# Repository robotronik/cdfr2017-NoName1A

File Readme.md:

$git clone https://github.com/robotronik/cdfr2017-NoName1A

$git add [les fichiers]
ou : $git add -u : tous les fichers modifiés

$git commit -m"le message de commit"

$git push origin master

$git pull origin master

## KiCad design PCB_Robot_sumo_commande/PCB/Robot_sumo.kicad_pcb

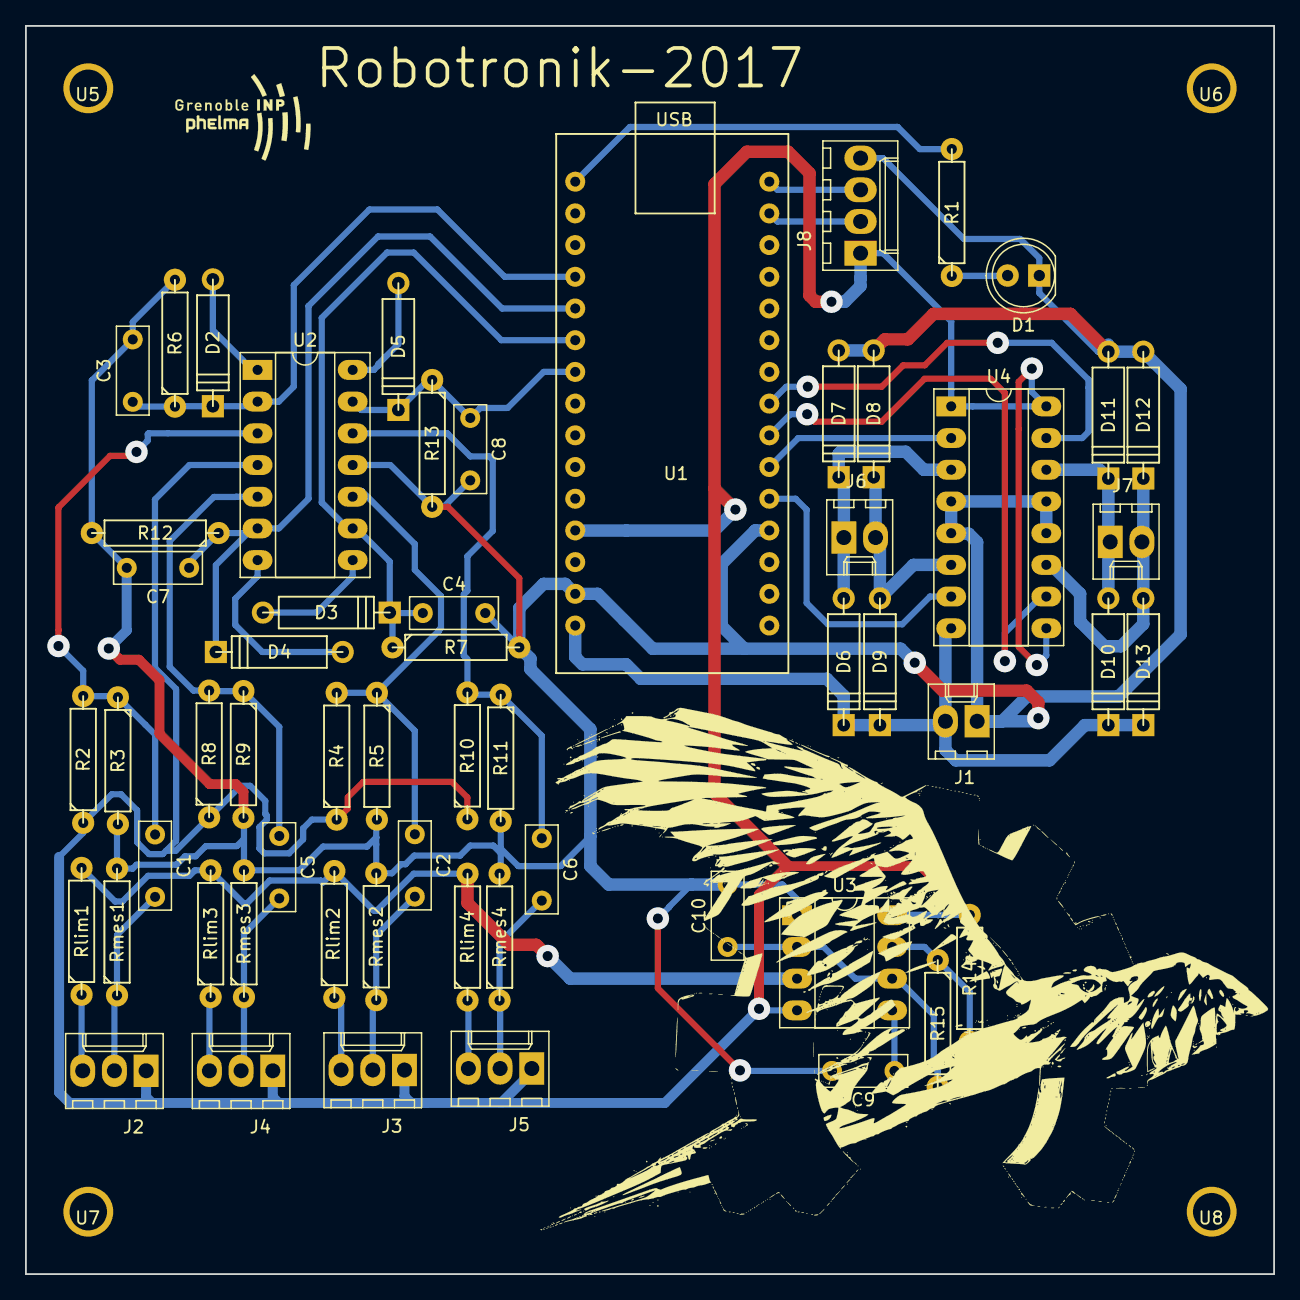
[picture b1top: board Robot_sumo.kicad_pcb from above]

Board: 2 copper layers, 100.0 x 100.0 mm, 62 parts (0 on the bottom side), 39 nets.

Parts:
C1, C2, C3, C4, C5, C6, C7, C8: C; C_Rect_L7.0mm_W2.5mm_P5.00mm
C9: 10nC; C_Rect_L7.0mm_W2.5mm_P5.00mm
C10: 4,8nC; C_Rect_L7.0mm_W2.5mm_P5.00mm
D1: LED; LED_D5.0mm
D2, D3, D4, D5: D; D4
D6, D7, D8, D9, D10, D11, D12, D13: D_ALT; D4
J1: CONN_Batt; Molex_KK-6410-02_02x2.54mm_Straight
J2: CONN_C1; Molex_KK-6410-03_03x2.54mm_Straight
J3: CONN_C3; Molex_KK-6410-03_03x2.54mm_Straight
J4: CONN_C2; Molex_KK-6410-03_03x2.54mm_Straight
J5: CONN_C4; Molex_KK-6410-03_03x2.54mm_Straight
J6: CONN_M1; Molex_KK-6410-02_02x2.54mm_Straight
J7: CONN_M2; Molex_KK-6410-02_02x2.54mm_Straight
J8: CONN_distance; Molex_KK-6410-04_04x2.54mm_Straight
R1, R2, R3, R4, R5, R6, R7, R8, R9, R10, R11, R12, R13: R; R4-LARGE_PADS
R14: 60kR; R4-LARGE_PADS
R15: 120kR; R4-LARGE_PADS
Rlim1, Rlim2, Rlim3, Rlim4: R; R4-LARGE_PADS
Rmes1, Rmes2, Rmes3, Rmes4: R; R4-LARGE_PADS
U1: Arduino-nano
U2: LM324; DIP-14_W7.62mm_Socket_LongPads
U3: NE555; DIP-8_W7.62mm_Socket_LongPads
U4: L293; DIP-16_W7.62mm_Socket_LongPads
U5, U6, U7, U8: Trou-3

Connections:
+5V: J2.1, J3.1, J4.1, J5.1, J8.1, R2.1, R4.1, R8.1, R10.1, R14.1, U1.12, U2.4, U3.4, U3.8, U4.1, U4.9, U4.16
/R-IR/C1: C3.1, D2.1, R6.1, U1.4, U2.2
/R-IR/C2: C7.1, D4.1, R12.1, U1.5, U2.6
/R-IR/C3: C4.1, D3.1, R7.1, U1.6, U2.9
/R-IR/C4: C8.1, D5.1, R13.1, U1.7, U2.13
/R-IR/Signal-e: Rlim1.2, Rlim2.2, Rlim3.2, Rlim4.2, U3.3
/distance_sensor/Echo: J8.3, U1.30
/distance_sensor/Trig: J8.2, U1.29
/motor-part/O1: U1.20, U4.7
/motor-part/O2: U1.22, U4.10
/motor-part/PWM1: U1.21, U4.2
/motor-part/PWM2: U1.23, U4.15
GND: C3.2, C4.2, C7.2, C8.2, C9.2, C10.2, D1.1, D7.2, D8.2, D11.2, D12.2, J1.1, J8.4, R3.2, R5.2, R6.2, R7.2, R9.2, R11.2, R12.2, R13.2, Rmes1.2, Rmes2.2, Rmes3.2, Rmes4.2, U1.14, U1.19, U2.11, U3.1, U4.4, U4.5, U4.12, U4.13
unnamed: C1.1, R2.2, R3.1, U2.3
unnamed: C1.2, J2.2, Rmes1.1
unnamed: C2.1, R4.2, R5.1, U2.10
unnamed: C2.2, J3.2, Rmes2.1
unnamed: C5.1, R8.2, R9.1, U2.5
unnamed: C5.2, J4.2, Rmes3.1
unnamed: C6.1, R10.2, R11.1, U2.12
unnamed: C6.2, J5.2, Rmes4.1
unnamed: C9.1, U3.5
unnamed: C10.1, R15.2, U3.2, U3.6
unnamed: D1.2, R1.1
unnamed: D2.2, U2.1
unnamed: D3.2, U2.8
unnamed: D4.2, U2.7
unnamed: D5.2, U2.14
unnamed: D6.2, D7.1, J6.1, U4.3
unnamed: D8.1, D9.2, J6.2, U4.6
unnamed: D10.2, D11.1, J7.1, U4.14
unnamed: D12.1, D13.2, J7.2, U4.11
unnamed: J2.3, Rlim1.1
unnamed: J3.3, Rlim2.1
unnamed: J4.3, Rlim3.1
unnamed: J5.3, Rlim4.1
unnamed: R1.2, U1.1
unnamed: R14.2, R15.1, U3.7
VCC: D6.1, D9.1, D10.1, D13.1, J1.2, U1.15, U4.8

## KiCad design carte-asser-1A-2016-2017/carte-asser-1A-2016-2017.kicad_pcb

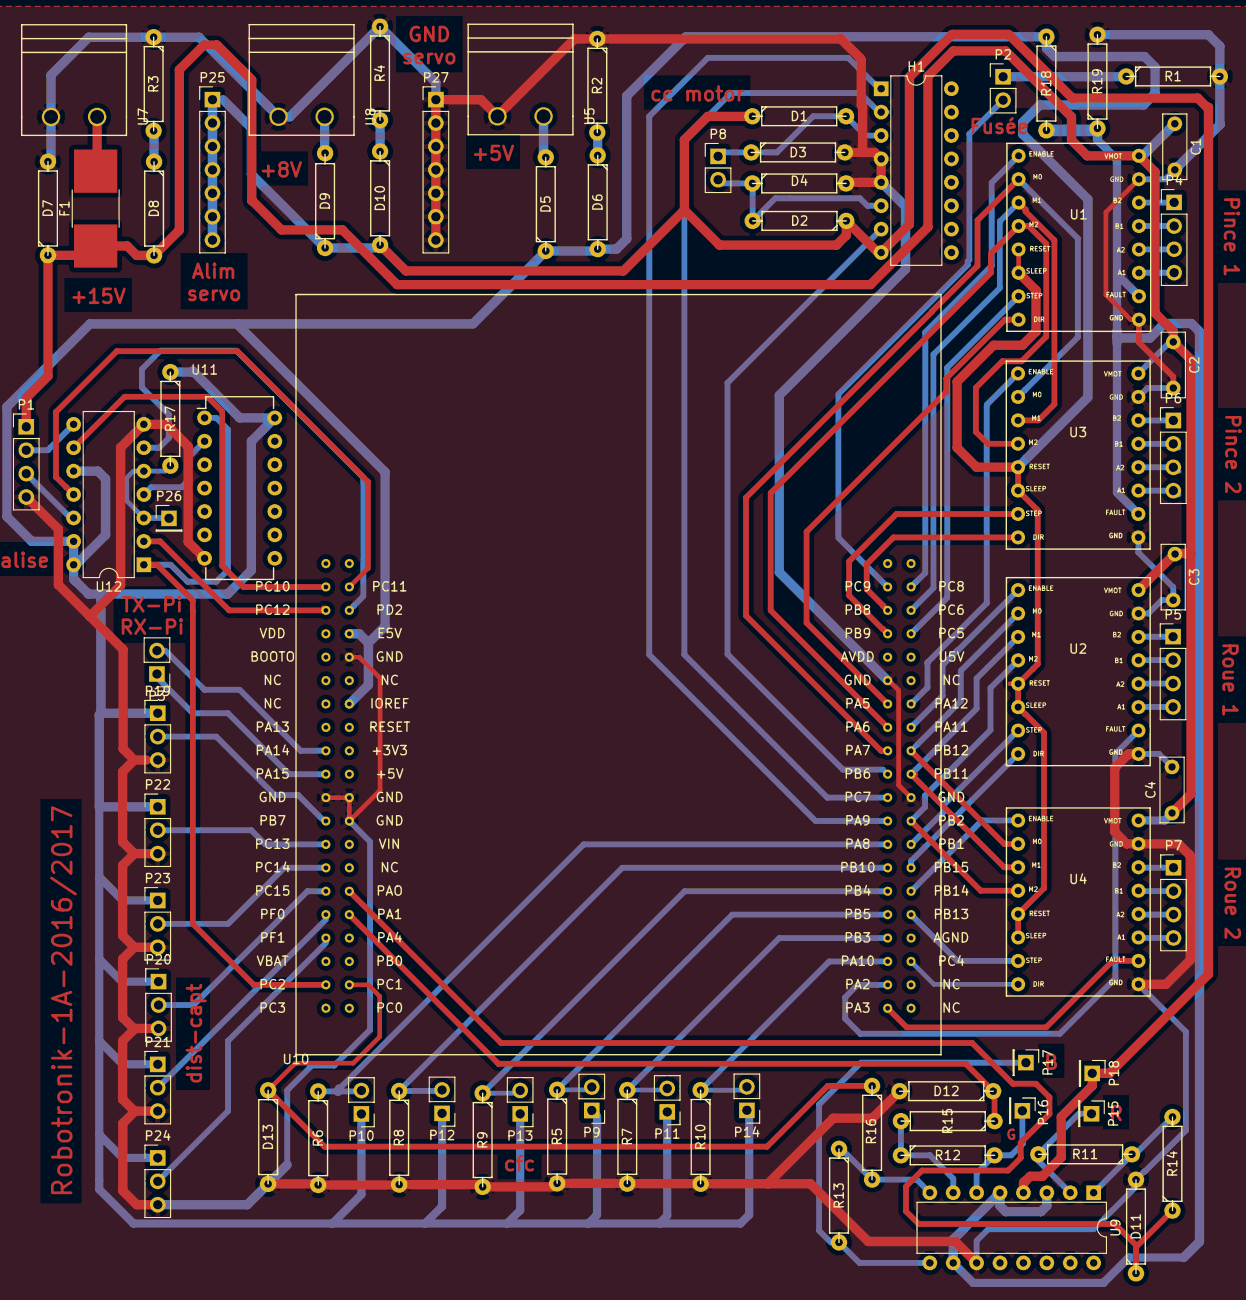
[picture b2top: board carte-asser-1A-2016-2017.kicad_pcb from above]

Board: 2 copper layers, 76 parts (0 on the bottom side), 86 nets.

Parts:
C1, C2, C3, C4: 100µ; C_Rect_L7.0mm_W2.5mm_P5.00mm
D1, D2, D3, D4, D7: D_Schottky; R4-LARGE_PADS
D5, D9: D_Small; R4-LARGE_PADS
D6, D8, D10: LED; R4-LARGE_PADS
D11, D12, D13: ZENER; R4-LARGE_PADS
F1: FUSE; R_2816_HandSoldering
H1: H-bridge; DIP-16_W7.62mm
P1: Balise; Pin_Header_Straight_1x04_Pitch2.54mm
P2: led-fusée; Pin_Header_Straight_1x02_Pitch2.54mm
P3: uart-pi; Pin_Header_Straight_1x02_Pitch2.54mm
P4: stepstick1; Pin_Header_Straight_1x04_Pitch2.54mm
P5: stepstick3; Pin_Header_Straight_1x04_Pitch2.54mm
P6: stepstick2; Pin_Header_Straight_1x04_Pitch2.54mm
P7: stepstick4; Pin_Header_Straight_1x04_Pitch2.54mm
P8: cc-motor; Pin_Header_Straight_1x02_Pitch2.54mm
P9: cfc4; Pin_Header_Straight_1x02_Pitch2.54mm
P10: cfc1; Pin_Header_Straight_1x02_Pitch2.54mm
P11: cfc5; Pin_Header_Straight_1x02_Pitch2.54mm
P12: cfc2; Pin_Header_Straight_1x02_Pitch2.54mm
P13: cfc3; Pin_Header_Straight_1x02_Pitch2.54mm
P14: cfc6; Pin_Header_Straight_1x02_Pitch2.54mm
P15: red-captor; Pin_Header_Straight_1x01_Pitch2.54mm
P16: green-captor; Pin_Header_Straight_1x01_Pitch2.54mm
P17: blue-captor; Pin_Header_Straight_1x01_Pitch2.54mm
P18: alim-color; Pin_Header_Straight_1x01_Pitch2.54mm
P19: dist-capt1; Pin_Header_Straight_1x03_Pitch2.54mm
P20: dist-capt4; Pin_Header_Straight_1x03_Pitch2.54mm
P21: dist-capt5; Pin_Header_Straight_1x03_Pitch2.54mm
P22: dist-capt2; Pin_Header_Straight_1x03_Pitch2.54mm
P23: dist-capt3; Pin_Header_Straight_1x03_Pitch2.54mm
P24: dist-capt6; Pin_Header_Straight_1x03_Pitch2.54mm
P25: alim-servo; Pin_Header_Straight_1x07_Pitch2.54mm
P26: data-servo; Pin_Header_Straight_1x01_Pitch2.54mm
P27: masse-servo; Pin_Header_Straight_1x07_Pitch2.54mm
R1, R14, R15, R16: 1k; R4-LARGE_PADS
R2: 300; R4-LARGE_PADS
R3: 1.3k; R4-LARGE_PADS
R4: 500; R4-LARGE_PADS
R5, R6, R7, R8, R9, R10: 10k; R4-LARGE_PADS
R11, R12: 100M; R4-LARGE_PADS
R13: 180M; R4-LARGE_PADS
R17: R; R4-LARGE_PADS
R18: 270; R4-LARGE_PADS
R19: 330; R4-LARGE_PADS
U1, U2, U3, U4: Stepstick
U5: +5V; B plug 5mm
U7: +15V; B plug 5mm
U8: +7.3V; B plug 5mm
U9: LM324; DIP-16_W7.62mm
U10: Nucleo-64
U11: 74HC04; DIP-14_W7.62mm
U12: 74LS126; DIP-14_W7.62mm

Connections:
+3V3: R18.2, R19.1, U1.10, U3.10, U9.3, U9.5, U9.10
+5V: D5.1, D6.2, P9.1, P10.1, P11.1, P12.1, P13.1, P14.1, P19.1, P20.1, P21.1, P22.1, P23.1, P24.1, R17.1, R18.1, U1.3, U1.4, U2.3, U2.4, U3.3, U3.4, U4.3, U4.4, U10.34, U10.37, U11.14, U12.10, U12.13, U12.14
+8V: D1.1, D2.1, D9.1, D10.2, H1.8, P18.1, P25.1, P25.2, P25.3, P25.4, P25.5, P25.6, P25.7, U9.4
+15V: C1.1, C2.1, C3.1, C4.1, D7.1, D8.2, F1.1, P1.1, U1.16, U2.16, U3.16, U4.16
/balise_part/Rx-balise: U10.39, U12.11
/balise_part/Tx-balise: U10.19, U12.9
/cfc_part/cfc1: P10.2, R6.1, U10.68
/cfc_part/cfc2: P12.2, R8.1, U10.67
/cfc_part/cfc3: P13.2, R9.1, U10.66
/cfc_part/cfc4: P9.2, R5.1, U10.65
/cfc_part/cfc5: P11.2, R7.1, U10.64
/cfc_part/cfc6: P14.2, R10.1, U10.63
/color_part/c_couleurB: D13.1, R16.1, U10.22
/color_part/c_couleurG: D12.1, R15.1, U10.25
/color_part/c_couleurR: D11.1, R14.1, U10.26
/command_part/Carte_Fault_1: U2.10, U10.62
/command_part/Carte_Fault_2: U4.10, U10.61
/command_part/RX-Pi: P3.1, U10.11
/command_part/RX-servo: U10.38, U12.6
/command_part/TX-Pi: P3.2, U10.12
/command_part/TX-servo: U10.18, U12.2
/command_part/c-distance1: P19.2, U10.9
/command_part/c-distance2: P22.2, U10.8
/command_part/c-distance3: P23.2, U10.7
/command_part/c-distance4: P20.2, U10.6
/command_part/c-distance5: P21.2, U10.5
/command_part/c-distance6: P24.2, U10.4
/command_part/dir-cc: H1.7, U10.71
/command_part/dir-p1: U1.1, U10.74
/command_part/dir-p2: U3.1, U10.78
/command_part/dir-r1: U2.1, U10.47
/command_part/dir-r2: U4.1, U10.43
/command_part/dir-servo: U10.2, U11.1, U12.1
/command_part/enable-cc: H1.1, U10.69
/command_part/enable-p1: U1.8, U10.59
/command_part/enable-p2: U3.8, U10.54
/command_part/enable-r1: U2.8, U10.53
/command_part/enable-r2: U4.8, U10.46
/command_part/led_fusée: P2.2, U10.79
/command_part/pince-M0: U1.7, U3.7, U10.72
/command_part/pince-M1: U1.6, U3.6, U10.58
/command_part/pince-M2: U1.5, U3.5, U10.73
/command_part/roue-M0: U2.7, U4.7, U10.52
/command_part/roue-M1: U2.6, U4.6, U10.51
/command_part/roue-M2: U2.5, U4.5, U10.49
/command_part/speed-cc: H1.2, U10.70
/command_part/step-p1: U1.2, U10.57
/command_part/step-p2: U3.2, U10.77
/command_part/step-r1: U2.2, U10.48
/command_part/step-r2: U4.2, U10.45
GND: C1.2, C2.2, C3.2, C4.2, D3.2, D4.2, D7.2, D11.2, D12.2, D13.2, H1.4, H1.5, P1.4, P19.3, P20.3, P21.3, P22.3, P23.3, P24.3, P27.1, P27.2, P27.3, P27.4, P27.5, P27.6, P27.7, R1.2, R2.1, R3.1, R4.1, R5.2, R6.2, R7.2, R8.2, R9.2, R10.2, R19.2, U1.9, U1.15, U2.9, U2.15, U3.9, U3.15, U4.9, U4.15, U5.2, U7.2, U8.2, U9.11, U10.10, U10.29, U10.30, U10.36, U10.50, U10.75, U11.7, U12.7
unnamed: D1.2, D3.1, H1.3, P8.1
unnamed: D2.2, D4.1, H1.6, P8.2
unnamed: D5.2, U5.1
unnamed: D6.1, R2.2
unnamed: D8.1, R3.2
unnamed: D9.2, U8.1
unnamed: D10.1, R4.2
unnamed: F1.2, U7.1
unnamed: P1.2, U12.8
unnamed: P1.3, U12.12
unnamed: P2.1, R1.1
unnamed: P4.1, U1.14
unnamed: P4.2, U1.13
unnamed: P4.3, U1.12
unnamed: P4.4, U1.11
unnamed: P5.1, U2.14
unnamed: P5.2, U2.13
unnamed: P5.3, U2.12
unnamed: P5.4, U2.11
unnamed: P6.1, U3.14
unnamed: P6.2, U3.13
unnamed: P6.3, U3.12
unnamed: P6.4, U3.11
unnamed: P7.1, U4.14
unnamed: P7.2, U4.13
unnamed: P7.3, U4.12
unnamed: P7.4, U4.11
unnamed: P15.1, R11.2, U9.2
unnamed: P16.1, R12.2, U9.6
unnamed: P17.1, R13.2, U9.9
unnamed: P26.1, R17.2, U12.3, U12.5
unnamed: R11.1, R14.2, U9.1
unnamed: R12.1, R15.2, U9.7
unnamed: R13.1, R16.2, U9.8
unnamed: U11.2, U12.4

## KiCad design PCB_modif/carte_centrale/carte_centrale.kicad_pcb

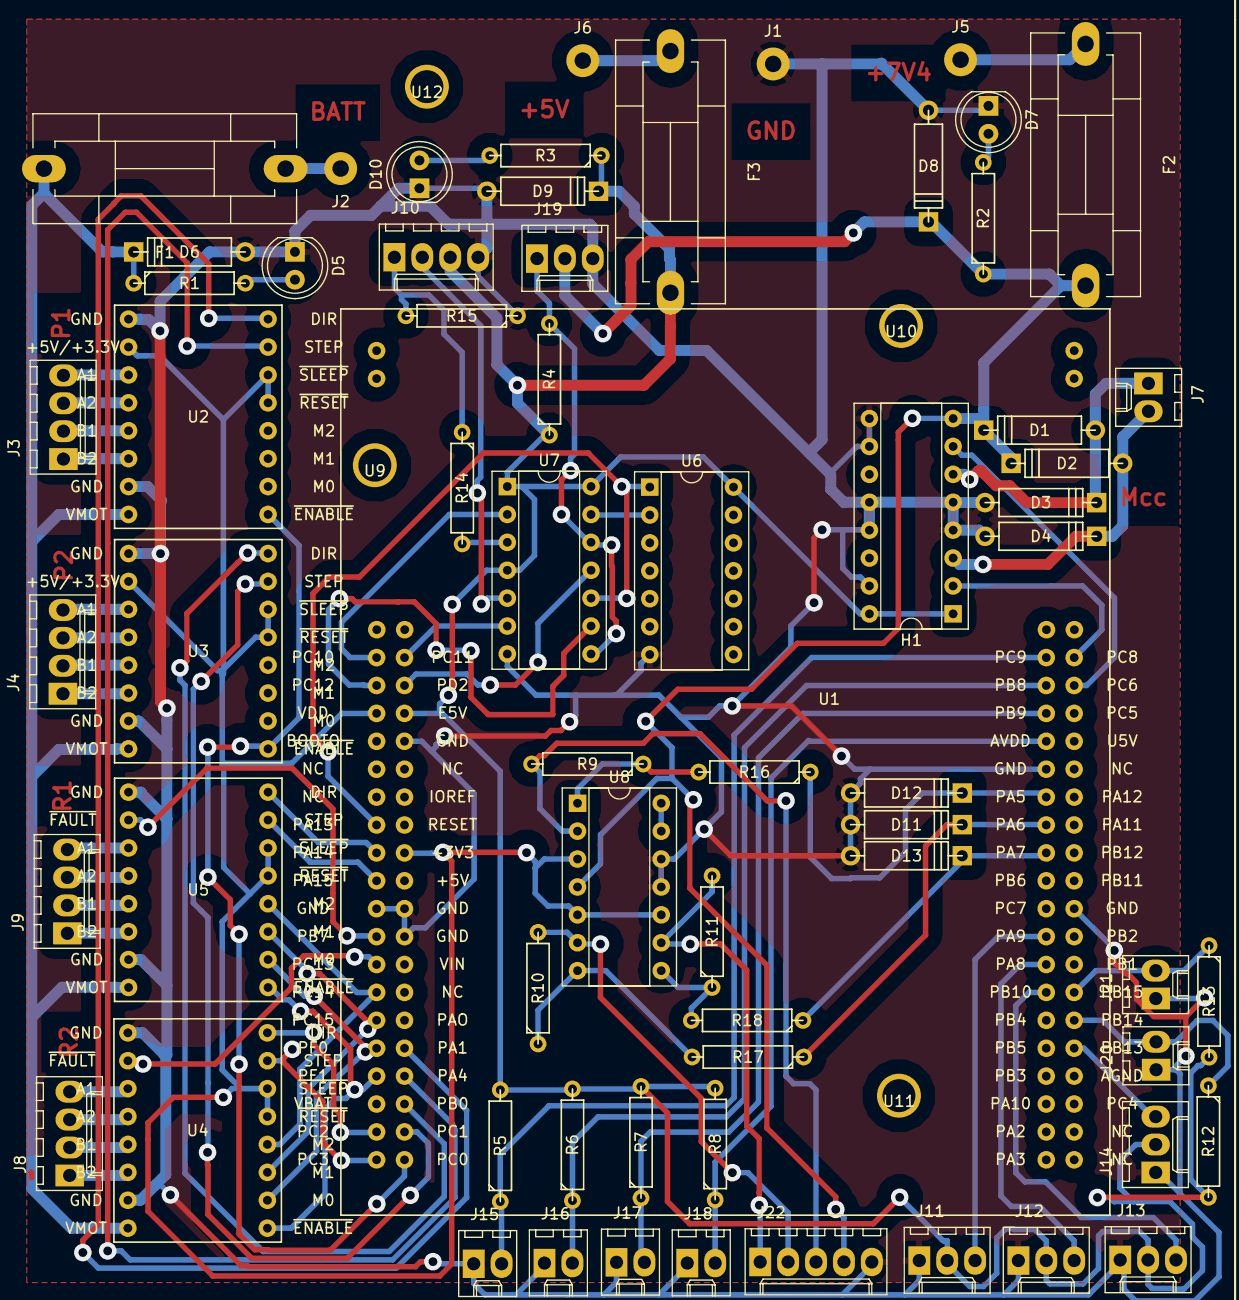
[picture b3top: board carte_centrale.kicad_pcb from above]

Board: 2 copper layers, 69 parts (0 on the bottom side), 76 nets.

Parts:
D1, D2, D3, D4, D6, D8, D9: D; D4
D5, D7, D10: LED; LED_D5.0mm
D11, D12, D13: D_Zener_3V3; D4
F1: Fuse_BATT; Fuseholder5x20_horiz_SemiClosed_Casing10x25mm
F2: Fuse_+7V4; Fuseholder5x20_horiz_SemiClosed_Casing10x25mm
F3: Fuse_+5V; Fuseholder5x20_horiz_SemiClosed_Casing10x25mm
H1: H-bridge; DIP-16_W7.62mm_Socket
J1: CONN_01X01_GND; Measurement_Point_Round-TH_Big
J2: CONN_01X01_BATT; Measurement_Point_Round-TH_Big
J3: CONN_01X04_pince1; Molex_KK-6410-04_04x2.54mm_Straight
J4: CONN_01X04_pince2; Molex_KK-6410-04_04x2.54mm_Straight
J5: CONN_01X01_+7V4; Measurement_Point_Round-TH_Big
J6: CONN_01X01_+5V; Measurement_Point_Round-TH_Big
J7: CONN_01X02_moteur_cc; Molex_KK-6410-02_02x2.54mm_Straight
J8: CONN_01X04_roue1; Molex_KK-6410-04_04x2.54mm_Straight
J9: CONN_01X04_roue2; Molex_KK-6410-04_04x2.54mm_Straight
J10: CONN_01X04_RASP; Molex_KK-6410-04_04x2.54mm_Straight
J11: CONN_01X03_D1; Molex_KK-6410-03_03x2.54mm_Straight
J12: CONN_01X03_D2; Molex_KK-6410-03_03x2.54mm_Straight
J13: CONN_01X03_D3; Molex_KK-6410-03_03x2.54mm_Straight
J14: CONN_01X03_D4; Molex_KK-6410-03_03x2.54mm_Straight
J15: CONN_01X02_FC1; Molex_KK-6410-02_02x2.54mm_Straight
J16: CONN_01X02_FC2; Molex_KK-6410-02_02x2.54mm_Straight
J17: CONN_01X02_FC3; Molex_KK-6410-02_02x2.54mm_Straight
J18: CONN_01X02_FC4; Molex_KK-6410-02_02x2.54mm_Straight
J19: CONN_01X03_SERVOS; Molex_KK-6410-03_03x2.54mm_Straight
J20: CONN_01X02_SELEC; Molex_KK-6410-02_02x2.54mm_Straight
J21: CONN_01X02_JACK; Molex_KK-6410-02_02x2.54mm_Straight
J22: CONN_01X05_couleur; Molex_KK-6410-05_05x2.54mm_Straight
R1: 2,7kR; R4
R2: 1,2kR; R4
R3: 680R; R4
R4: 5,6kR; R4
R5, R6, R7, R8, R12, R13, R16, R17, R18: 10kR; R4
R9, R10, R11: 5MR; R4
R14: 1.8kR; R4
R15: 2.7kR; R4
U1: Nucleo-64
U2, U3: Stepstick; step_stick
U4, U5: Stepstick_gros; step_stick_gros
U6: 74HC04; DIP-14_W7.62mm_Socket
U7: 74LS126; DIP-14_W7.62mm_Socket
U8: LM324; DIP-14_W7.62mm_Socket
U9, U10, U11, U12: trou-d3mm; trou_d3mm

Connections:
1A: H1.2, U1.59
2A: H1.7, U1.58
+3V3: U1.17, U1.32, U2.3, U2.4, U2.10, U3.3, U3.4, U3.10, U4.3, U4.4, U5.3, U5.4, U8.3, U8.5, U8.10
+5V: F3.1, J6.1
+5V_P: D9.1, F3.2, H1.1, H1.16, J10.3, J11.2, J12.2, J13.2, J14.2, R3.1, R4.1, R5.2, R6.2, R7.2, R8.2, R12.2, R13.2, U1.37, U6.14, U7.1, U7.4, U7.14
+7V4: F2.1, J5.1
+7V4_P: D1.1, D2.1, D8.1, F2.2, H1.8, J19.2, J22.4, R2.1, U8.4
BATT: F1.1, J2.1
BATT_P: D6.1, F1.2, R1.1, U2.16, U3.16, U4.16, U5.16
C-1: D12.1, R16.1, U1.74
C-2: D11.1, R17.1, U1.73
C-3: D13.1, R18.1, U1.72
GND: D3.2, D4.2, D5.1, D6.2, D7.1, D8.2, D9.2, D10.1, D11.2, D12.2, D13.2, H1.4, H1.5, H1.9, H1.10, H1.12, H1.13, H1.15, J1.1, J10.4, J11.1, J12.1, J13.1, J14.1, J15.1, J16.1, J17.1, J18.1, J19.3, J20.1, J21.1, J22.5, R15.1, U1.10, U1.29, U1.30, U1.36, U1.50, U1.75, U2.9, U2.15, U3.9, U3.15, U4.9, U4.15, U5.9, U5.15, U6.7, U7.7, U8.11, U8.12
unnamed: D1.2, D3.1, H1.6, J7.1
unnamed: D2.2, D4.1, H1.3, J7.2
unnamed: D5.2, R1.2
unnamed: D7.2, R2.2
unnamed: D10.2, R3.2
unnamed: J3.1, U2.14
unnamed: J3.2, U2.13
unnamed: J3.3, U2.12
unnamed: J3.4, U2.11
unnamed: J4.1, U3.14
unnamed: J4.2, U3.13
unnamed: J4.3, U3.12
unnamed: J4.4, U3.11
unnamed: J8.1, U4.14
unnamed: J8.2, U4.13
unnamed: J8.3, U4.12
unnamed: J8.4, U4.11
unnamed: J9.1, U5.14
unnamed: J9.2, U5.13
unnamed: J9.3, U5.12
unnamed: J9.4, U5.11
unnamed: J10.1, R14.1, R15.2
unnamed: J10.2, U7.5
unnamed: J19.1, R4.2, U7.8, U7.12
unnamed: J22.1, R11.2, U8.9
unnamed: J22.2, R10.2, U8.6
unnamed: J22.3, R9.2, U8.2
unnamed: R10.1, R17.2, U8.7
unnamed: R11.1, R18.2, U8.8
unnamed: R14.2, U7.3
unnamed: R9.1, R16.2, U8.1
unnamed: U1.1, U4.2
unnamed: U1.2, U4.1
unnamed: U1.4, U4.8, U5.8
unnamed: U1.5, U4.7, U5.7
unnamed: U1.6, U4.6, U5.6
unnamed: U1.7, U4.5, U5.5
unnamed: U1.8, U4.10
unnamed: U1.9, U5.10
unnamed: U1.11, U5.2
unnamed: U1.12, U5.1
unnamed: U1.21, U2.8, U3.8
unnamed: U1.22, U3.2
unnamed: U1.23, U3.1
unnamed: U1.24, U2.2
unnamed: U1.25, U2.1
unnamed: U6.2, U7.13
unnamed: U8.13, U8.14
RX_RASP: U1.39, U7.6
RX_XL: U1.38, U7.11
TX_RASP: U1.19, U7.2
TX_XL: U1.18, U7.9
dist_1: J11.3, U1.69
dist_2: J12.3, U1.68
dist_3: J13.3, U1.67
dist_4: J14.3, U1.45
fc_1: J15.2, R5.1, U1.79
fc_2: J16.2, R6.1, U1.78
fc_3: J17.2, R7.1, U1.77
fc_4: J18.2, R8.1, U1.76
jack: J21.2, R13.1, U1.47
selec: J20.2, R12.1, U1.46
sens_XL: U1.13, U6.1, U7.10

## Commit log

2016-12-15 first version of readme.md
2016-12-15 add reason
2016-12-15 Readme.md: instructions pour git
2016-12-15 premiers fichiers
2016-12-18 install_freecad
2017-01-19 c'est presque fini
2017-01-26 Nucleo-64
2017-01-28 Pièces à découper en alu
2017-01-28 Fichier dxf
2017-01-30 Fichiers dxf
2017-02-01 Debut carte actionneurs 1A
2017-02-02 suite pcb
2017-02-07 version finale (sans balises)
2017-02-09 suite pcb 2
2017-02-09 installation de mbed
2017-02-16 tests nucleo 32
2017-02-16 Fin PCB
2017-02-17 pièces du site reprap
2017-02-17 Gotronic
2017-02-18 petite modif
2017-02-18 encore une modif
2017-02-18 pieces dxf pour Eitarc
2017-02-19 visserie
2017-02-27 commande RS
2017-03-02 modif
2017-03-02 ajout
2017-03-02 profilés
2017-03-15 début tests
2017-03-15 c'était pas les bons fichiers :(
2017-03-28 pièces à découper dans le plexi
2017-03-29 suppression traits internes
2017-03-29 regroupement
2017-05-06 dernière commande RS
2017-05-06 ajout résistances
2017-05-07 ajout piles
2017-05-09 gnan
2017-05-09 Revert "gnan"
    This reverts commit a866e827c0ace1ce581c8c9d2953b4150d204266.
2017-05-09 Revert "ajout piles"
    This reverts commit 78f905b286f861724ea05db66121bbdf75669857.
2017-05-09 Revert "ajout résistances"
    This reverts commit 46b81a2bd47e0656bb7f7e7a92ee33fc6423a2a9.
2017-05-09 Commandes
2017-05-11 code pour capteurs de distance et Makefile
2017-05-14 gnaaaaaaaaaaaaaaaaaaaaaaaaaaaaaaaaaaaaaaaaaaaaaaaaaaaaaaaaaaaaaaaaaaa!
2017-06-18 pcb pour robot sumo
2017-06-20 ajout de logos et mise aux dimensions
2017-06-20 espacement modifié
2017-06-21 back logo
2017-07-01 last version I hope
2017-07-01 plan de masse
2017-07-02 changed some track under some capacitor and resistor
2017-07-05 added keepout area to erase copper pour glitch
2017-07-06 changed area keepout shape + corrected a track width error
2017-07-08 Removing duplicates
2017-07-08 useless files deleted
2017-07-08 reorganization
2017-07-09 CDFR_2018!
2017-08-30 components values
2017-09-07 set local time
2017-09-19 footprints
2019-09-08 code of CDFR-2017, NEVER REPRODUCE THIS
